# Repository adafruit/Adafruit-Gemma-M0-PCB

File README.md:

## Adafruit Gemma M0 PCB

<a href="http://www.adafruit.com/products/3501"><br/>
Click here to purchase one from the Adafruit shop</a>

PCB files for the Adafruit Gemma M0. 

This is the CAD & PCB data for the Adafruit Gemma. PCB format is EagleCAD schematic and board layout

For more details, check out the product page at
* https://www.adafruit.com/products/3501

### Description

The Adafruit Gemma M0 is a super small microcontroller board, with just enough built-in to create many simple projects. It may look small and cute: round, about the size of a quarter, with friendly alligator-clip sew pads. But do not be fooled! The Gemma M0 is incredibly powerful! We've taken the same form factor we used for the original ATtiny85-based Gemma and gave it an upgrade. The Gemma M0 has swapped out the lightweight ATtiny85 for a ATSAMD21E18 powerhouse.

The Gemma M0 will super-charge your wearables! It's just as small, and it's easier to use, so you can do more.

The most exciting part of the Gemma M0 is that while you can use it with the Arduino IDE, we are shipping it with CircuitPython on board. When you plug it in, it will show up as a very small disk drive with main.py on it. Edit main.py with your favorite text editor to build your project using Python, the most popular programming language. No installs, IDE or compiler needed, so you can use it on any computer, even ChromeBooks or computers you can't install software on. When you're done, unplug the Gemma M0 and your code will go with you.

### License

Adafruit invests time and resources providing this open source design, please support Adafruit and open-source hardware by purchasing products from [Adafruit](https://www.adafruit.com)!

Designed by Limor Fried/Ladyada for Adafruit Industries.

Creative Commons Attribution/Share-Alike, all text above must be included in any redistribution. See license.txt for additional details.

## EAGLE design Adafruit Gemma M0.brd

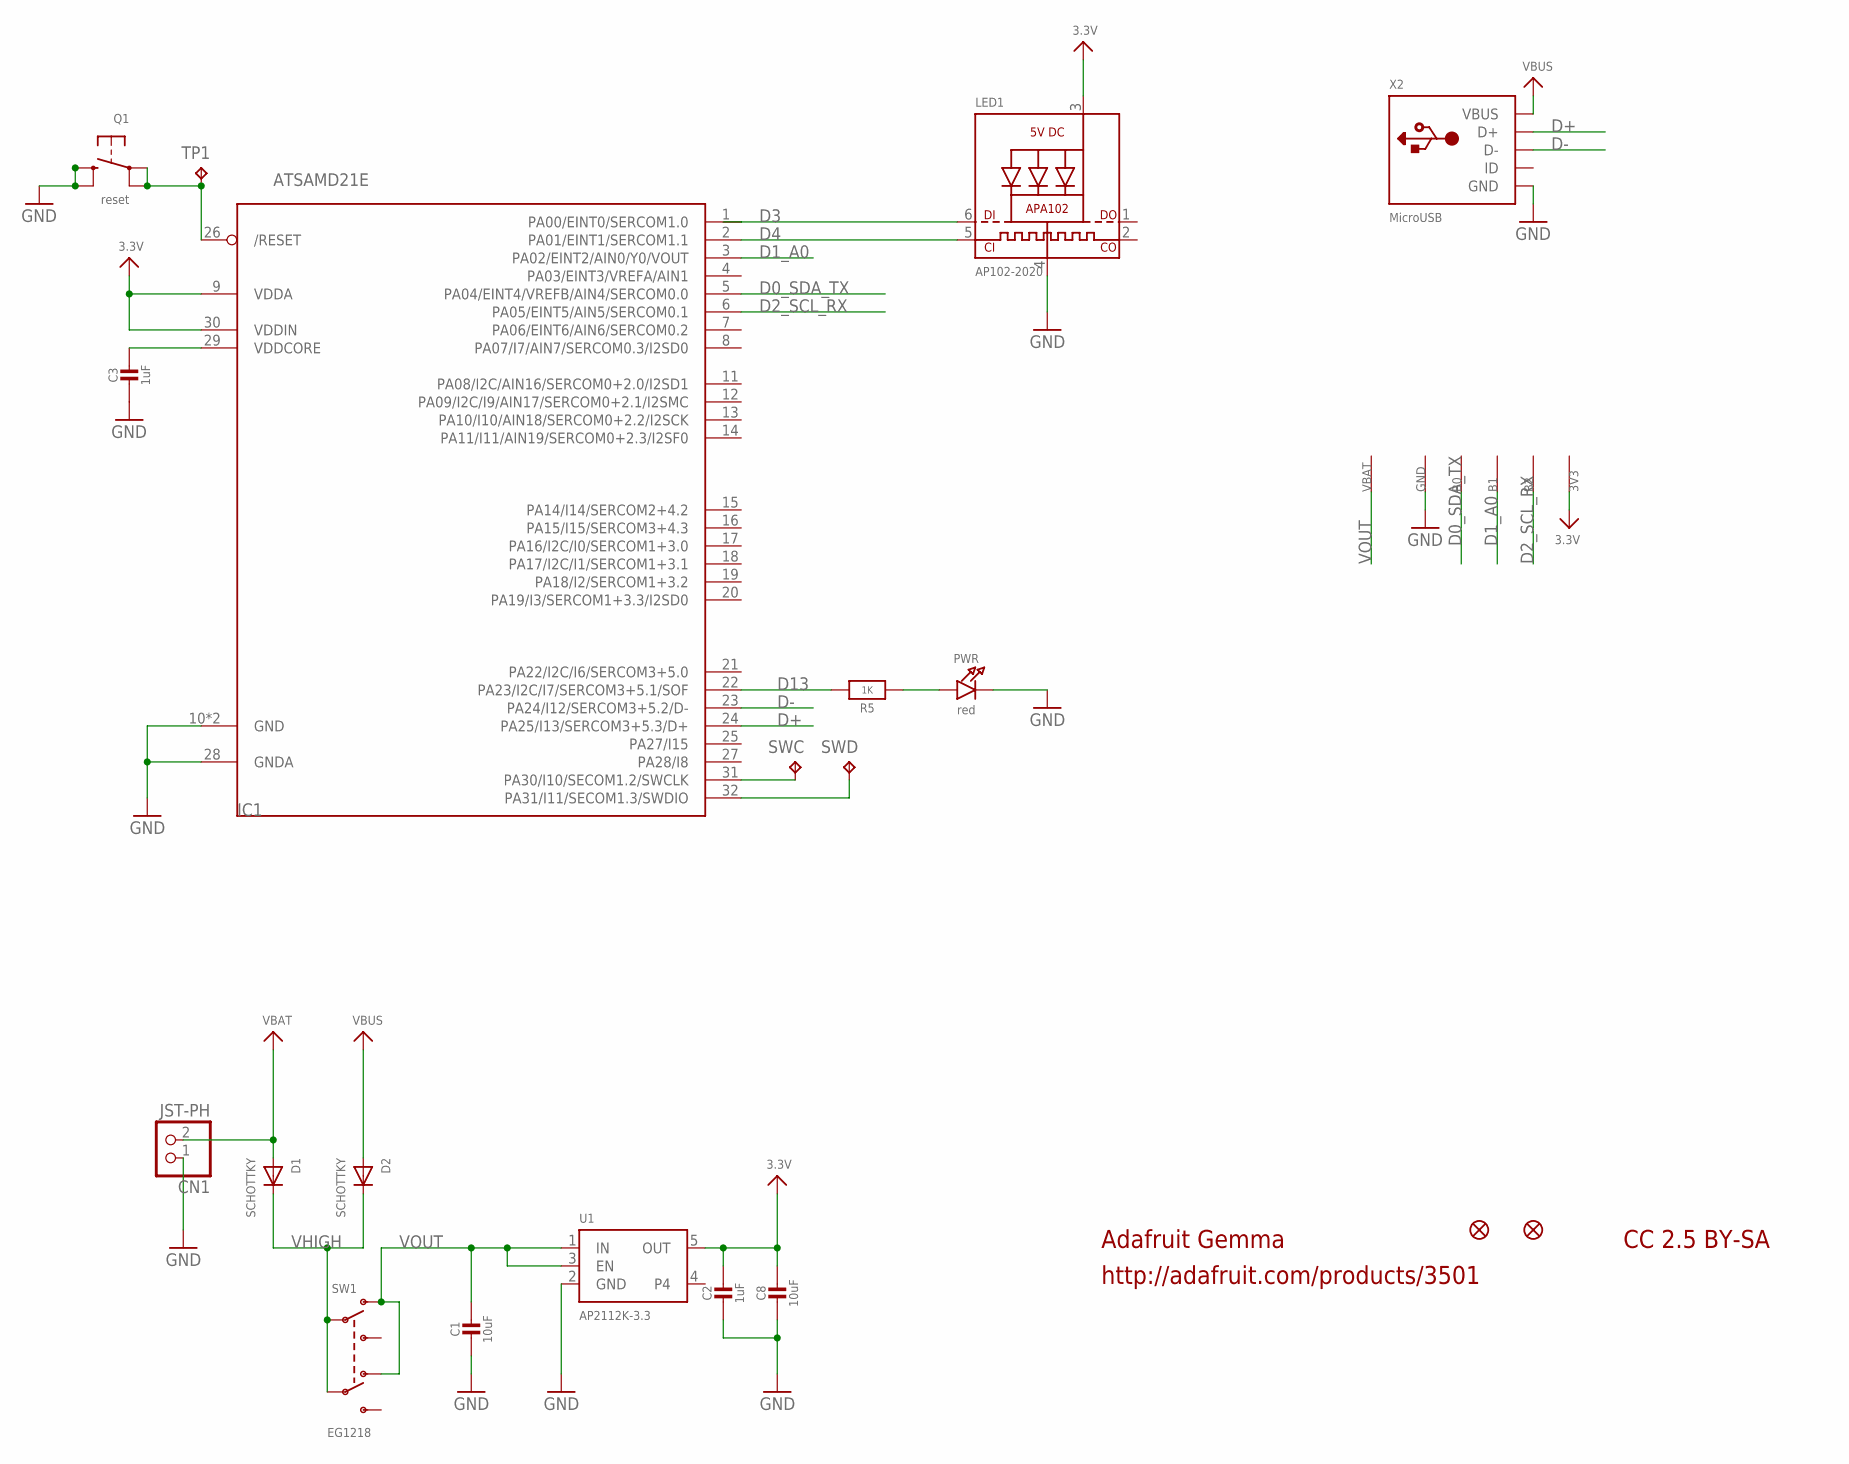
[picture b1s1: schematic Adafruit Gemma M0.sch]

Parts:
3V3: SEWTAP-ALLIGATOR; SEWALLI
B0, B1, B2: SEWTAP-ALLIGATOR; SEWALLI
C1, C8: 10uF; 0805-NO
C2, C3: 1uF; 0603-NO
CN1: JST-PH; JSTPH2
D1, D2: SCHOTTKY; SOD-123FL
GND: SEWTAP-ALLIGATOR; SEWALLI
IC1: ATSAMD21E; QFN32_5MM
LED1: AP102-2020; APA102_2020
PWR: red; CHIPLED_0603_NOOUTLINE
Q1: reset; BTN_KMR2_4.6X2.8
R5: 1K; 0603-NO
SW1: EG1218; EG1390
SWC: TPTP15R; TP15R
SWD: TPTP15R; TP15R
TP1: TPTP16R; TP16R
U1: AP2112K-3.3; SOT23-5
U$1, U$6: FIDUCIAL_1MM
VBAT: SEWTAP-ALLIGATOR; SEWALLI
X2: MicroUSB; 4UCONN_20329_V2

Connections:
3.3V: 3V3.P$1, C2.1, C8.1, IC1.9 (VDDA), IC1.30 (VDDIN), LED1.3 (VDD), U1.5 (OUT)
!RESET: IC1.26 (/RESET), Q1.A, Q1.A' (P1), TP1.TP
D0_SDA_TX: B0.P$1, IC1.5 (PA04/EINT4/VREFB/AIN4/SERCOM0.0)
D1_A0: B1.P$1, IC1.3 (PA02/EINT2/AIN0/Y0/VOUT)
D2_SCL_RX: B2.P$1, IC1.6 (PA05/EINT5/AIN5/SERCOM0.1)
D3: IC1.1 (PA00/EINT0/SERCOM1.0), LED1.6 (DI)
D4: IC1.2 (PA01/EINT1/SERCOM1.1), LED1.5 (CKI)
D13: IC1.22 (PA23/I2C/I7/SERCOM3+5.1/SOF), R5.2
D+: IC1.24 (PA25/I13/SERCOM3+5.3/D+), X2.D+
D-: IC1.23 (PA24/I12/SERCOM3+5.2/D-), X2.D-
GND: C1.2, C2.2, C3.2, C8.2, CN1.1, GND.P$1, IC1.10 (GND), IC1.28 (GNDA), IC1.33 (GND), LED1.4 (GND), PWR.C, Q1.B (S), Q1.B' (S1), U1.2 (GND), X2.BASE@1 (GND), X2.BASE@2 (GND), X2.GND, X2.SPRT@1 (GND), X2.SPRT@2 (GND), X2.SPRT@3 (GND), X2.SPRT@4 (GND)
unnamed: PWR.A, R5.1
SWCLK: IC1.31 (PA30/I10/SECOM1.2/SWCLK), SWC.TP
SWDIO: IC1.32 (PA31/I11/SECOM1.3/SWDIO), SWD.TP
VBAT: CN1.2, D1.A
VBUS: D2.A, X2.VBUS
VDDCORE: C3.1, IC1.29 (VDDCORE)
VHIGH: D1.C, D2.C, SW1.P1, SW1.P2
VOUT: C1.1, SW1.O1, SW1.O2, U1.1 (IN), U1.3 (EN), VBAT.P$1

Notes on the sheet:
Adafruit Gemma
http://adafruit.com/products/3501
CC 2.5 BY-SA

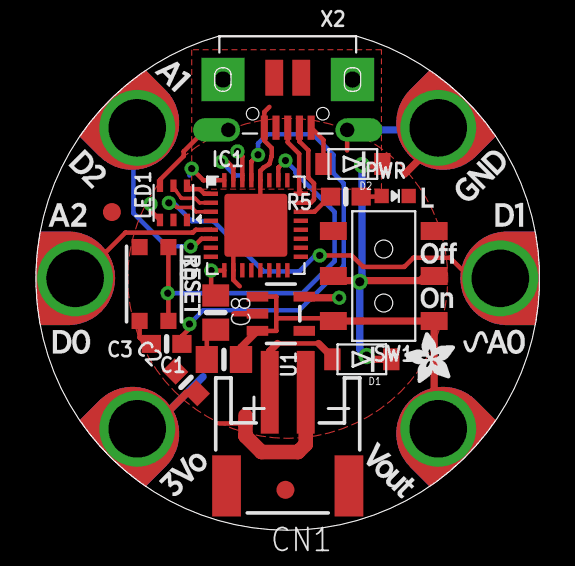
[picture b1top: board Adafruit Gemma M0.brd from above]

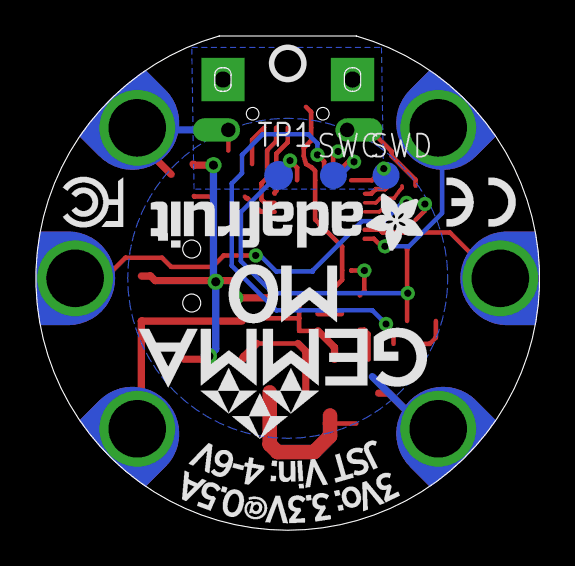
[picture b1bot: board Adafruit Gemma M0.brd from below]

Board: 2 copper layers, 28.0 x 27.5 mm, 29 parts (5 on the bottom side), 19 nets.

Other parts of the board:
U$7: GEMMA_M0_BOTTOM
U$8: GEMMA_M0_TOP
U$10: PCBFEAT-REV-040

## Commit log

2017-07-26 init
2021-05-18 Add pinout PDF

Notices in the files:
parts and their libraries:
microbuilder: This work is placed in the public domain, and may be freely used for commercial and non-commercial work with the following conditions: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
